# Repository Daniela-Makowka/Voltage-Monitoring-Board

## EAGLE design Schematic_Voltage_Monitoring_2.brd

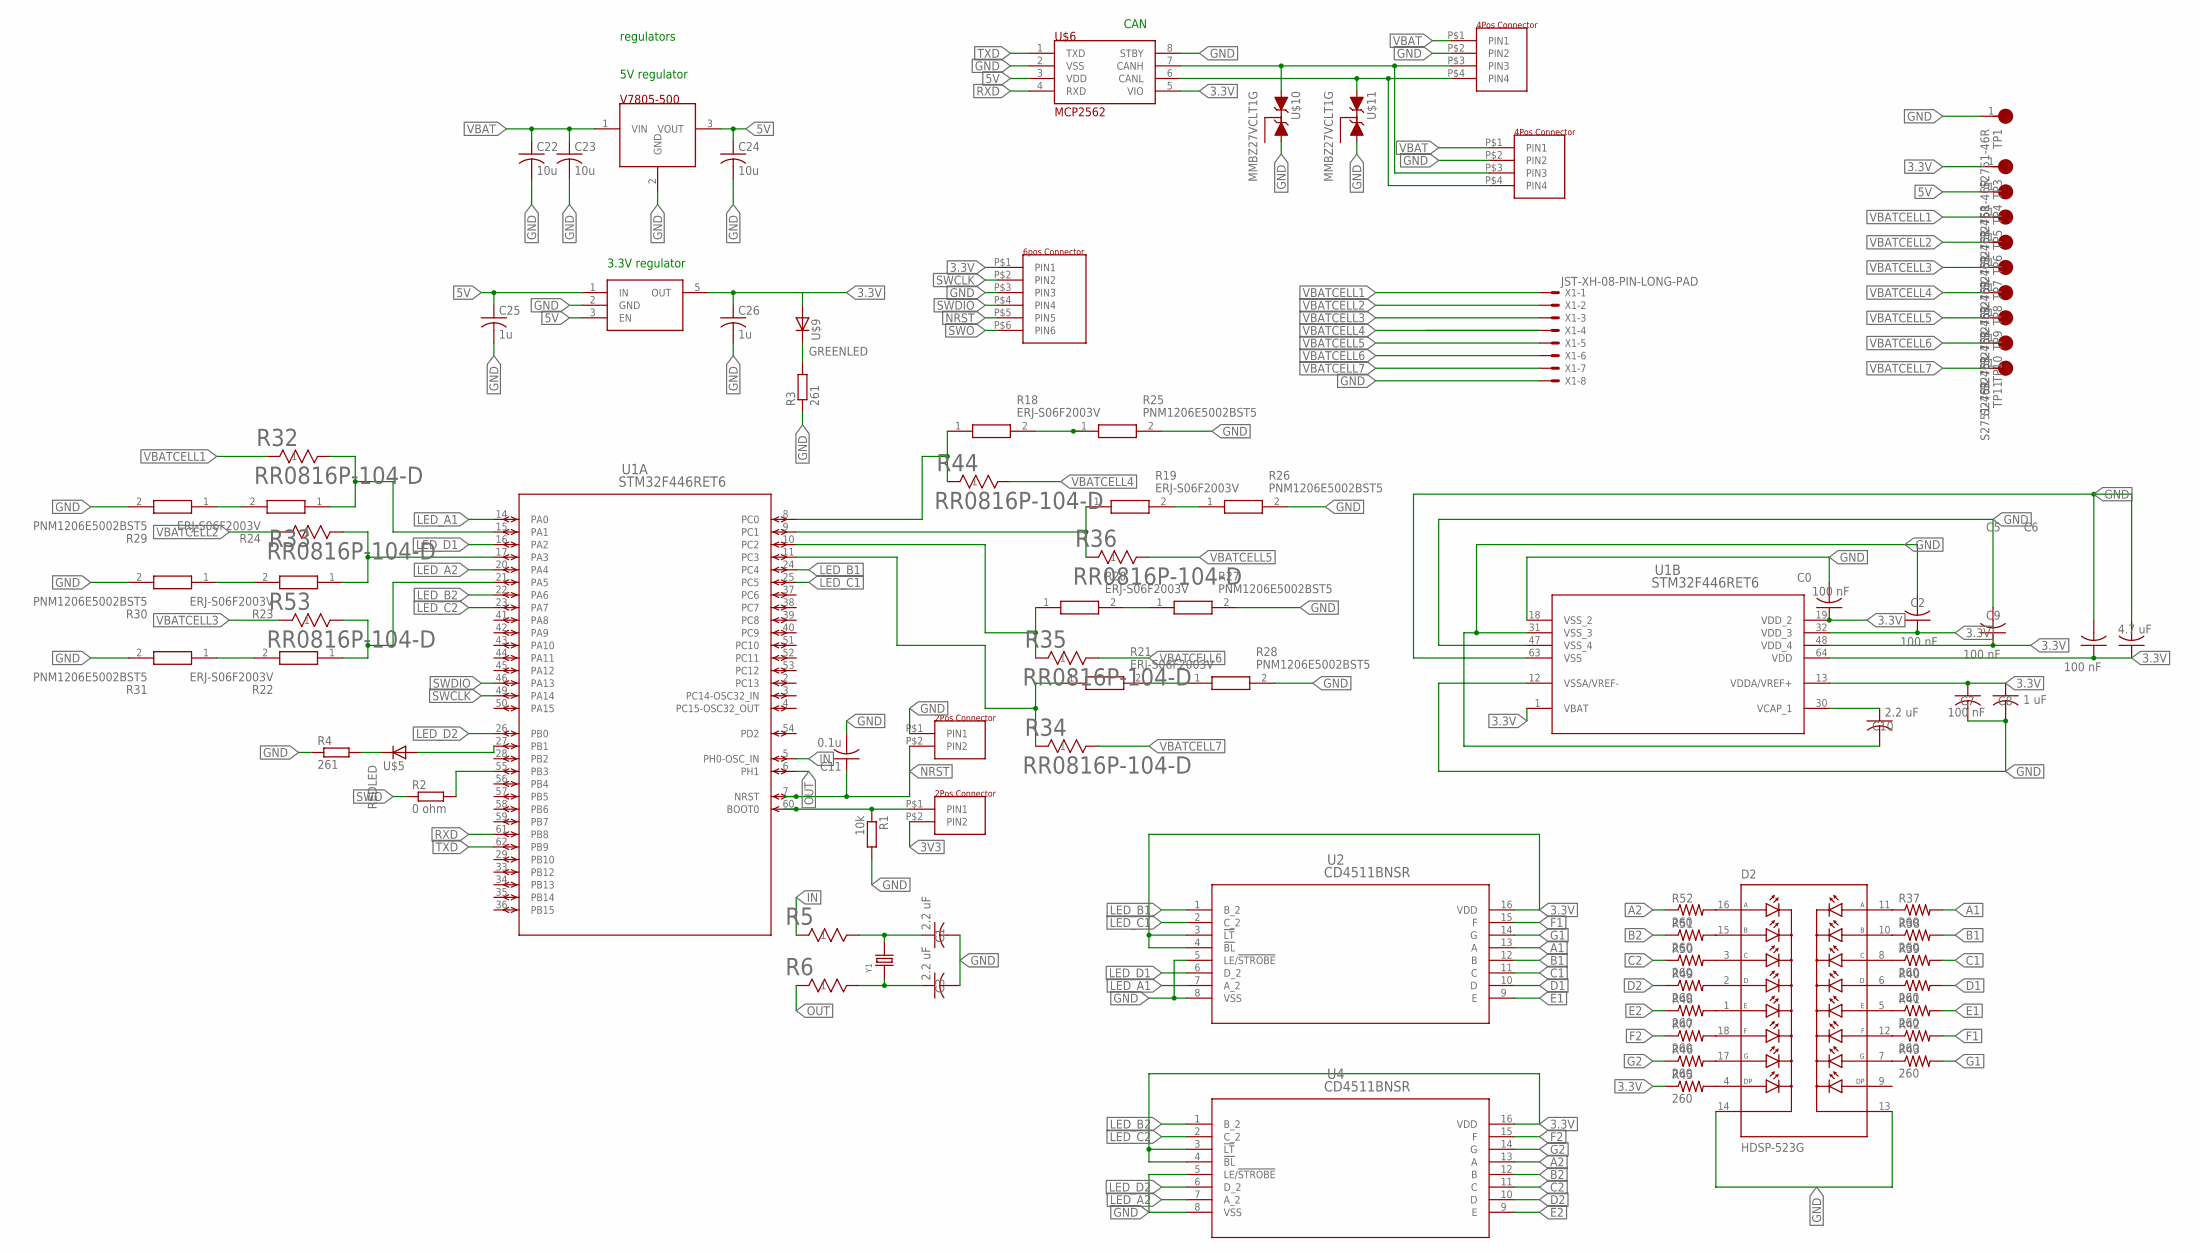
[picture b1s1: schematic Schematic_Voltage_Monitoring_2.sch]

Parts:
C0, C2, C5, C7, C9: 100 nF; C0603
C1, C3, C10: 2.2 uF; C0603
C6: 4.7 uF; C0603
C8: 1 uF; C0603
C11: 0.1u; C1206K
C22, C23, C24: 10u; C1206K
C25, C26: 1u; C1206K
D2: HDSP-523G; LED_HDSP-523G
R1: 10k; R0603
R2: 0 ohm; R0603
R3, R4: 261; R0603
R5, R6, R32, R33, R34, R35, R36, R44, R53: RR0816P-104-D; RES_0816_SUS
R18, R19, R20, R21, R22, R23, R24: ERJ-S06F2003V; ERJS06_U06_(0805)
R25, R26, R27, R28, R29, R30, R31: PNM1206E5002BST5; RESC3216X71N
R37, R38, R39, R40, R41, R42, R43, R45, R46, R47, R48, R49, R50, R51, R52: 260; R0603
TP1, TP3, TP4, TP5, TP6, TP7, TP8, TP9, TP10, TP11: S2751-46R; HARWIN_S2751-46R
U1: STM32F446RET6; LQFP64-10X10MM
U2, U4: CD4511BNSR; NS16
U$1, U$2: 4POS_CONNECTORMOLEX_MICROFIT3.0_RA_4PIN_2ROW; MOLEX_MICROFIT3.0_0430450400
U$3: 6POS_CONNECTOR.1"PITCH_HEADERS; 6POS_HEADER_.1"
U$4, U$7: 2POS_CONNECTOR,.1"HEADER; 2POS_HEADER_.1"
U$5, U$9: LED06033D_0603; LEDC1608X35
U$6: MCP2562; SOIC8
U$8: V7805-500; SIP3
U$10, U$11: MMBZ27VCLT1G; SOT23
U$23: TLV70233DBVR; SOT-23-5
X1: JST-XH-08-PIN-LONG-PAD; JST-XH-08-PACKAGE-LONG-PAD
Y1: DIP-CRYSTAL-16MHZ-18PF-30PPM-40R(HC49US); HC49US

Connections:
3.3V: C0.1, C2.1, C5.1, C6.1, C7.1, C8.1, C9.1, C26.1, R45.1, TP3.1, U1.1 (VBAT), U1.13 (VDDA/VREF+), U1.19 (VDD_2), U1.32 (VDD_3), U1.48 (VDD_4), U1.64 (VDD), U2.3 (!LT), U2.4 (!BL), U2.16 (VDD), U4.3 (!LT), U4.4 (!BL), U4.16 (VDD), U$3.P$1 (PIN1), U$6.5 (VIO), U$9.A, U$23.5 (OUT)
3V3: U$7.P$2 (PIN2)
5V: C24.1, C25.1, TP4.1, U$6.3 (VDD), U$8.3 (VOUT), U$23.1 (IN), U$23.3 (EN)
A1: R37.2, U2.13 (A)
A2: R52.1, U4.13 (A)
B1: R38.2, U2.12 (B)
B2: R51.1, U4.12 (B)
C1: R39.2, U2.11 (C)
C2: R50.1, U4.11 (C)
CANH: U$1.P$3 (PIN3), U$2.P$3 (PIN3), U$6.7 (CANH), U$10.1 (A1)
CANL: U$1.P$4 (PIN4), U$2.P$4 (PIN4), U$6.6 (CANL), U$11.1 (A1)
D1: R40.2, U2.10 (D)
D2: R49.1, U4.10 (D)
E1: R41.2, U2.9 (E)
E2: R48.1, U4.9 (E)
F1: R42.2, U2.15 (F)
F2: R47.1, U4.15 (F)
G1: R43.2, U2.14 (G)
G2: R46.1, U4.14 (G)
GND: C0.2, C1.2, C2.2, C3.2, C5.2, C6.2, C7.2, C8.2, C9.2, C10.2, C11.2, C22.2, C23.2, C24.2, C25.2, C26.2, D2.13 (COM2), D2.14 (COM1), R1.2, R3.1, R4.1, R25.2, R26.2, R27.2, R28.2, R29.2, R30.2, R31.2, TP1.1, U1.12 (VSSA/VREF-), U1.18 (VSS_2), U1.31 (VSS_3), U1.47 (VSS_4), U1.63 (VSS), U2.5 (LE/!STROBE), U2.8 (VSS), U4.5 (LE/!STROBE), U4.8 (VSS), U$1.P$2 (PIN2), U$2.P$2 (PIN2), U$3.P$3 (PIN3), U$4.P$1 (PIN1), U$6.2 (VSS), U$6.8 (STBY), U$8.2 (GND), U$10.2 (A2), U$11.2 (A2), U$23.2 (GND), X1.8
GREENLED: R3.2, U$9.C
IN: R5.1, U1.5 (PH0-OSC_IN)
LED_A1: U1.14 (PA0), U2.7 (A_2)
LED_A2: U1.20 (PA4), U4.7 (A_2)
LED_B1: U1.24 (PC4), U2.1 (B_2)
LED_B2: U1.22 (PA6), U4.1 (B_2)
LED_C1: U1.25 (PC5), U2.2 (C_2)
LED_C2: U1.23 (PA7), U4.2 (C_2)
LED_D1: U1.16 (PA2), U2.6 (D_2)
LED_D2: U1.26 (PB0), U4.6 (D_2)
unnamed: C10.1, U1.30 (VCAP_1)
unnamed: R1.1, U1.60 (BOOT0), U$7.P$1 (PIN1)
unnamed: R2.2, U1.55 (PB3)
unnamed: R19.1, R36.1, U1.9 (PC1)
unnamed: U1.27 (PB1), U$5.A
unnamed: C1.1, R5.2, Y1.2
unnamed: C3.1, R6.2, Y1.1
unnamed: D2.11 (A2), R37.1
unnamed: D2.10 (B2), R38.1
unnamed: D2.8 (C2), R39.1
unnamed: D2.6 (D2), R40.1
unnamed: D2.5 (E2), R41.1
unnamed: D2.12 (F2), R42.1
unnamed: D2.7 (G2), R43.1
unnamed: D2.4 (DP1), R45.2
unnamed: D2.17 (G1), R46.2
unnamed: D2.18 (F1), R47.2
unnamed: D2.1 (E1), R48.2
unnamed: D2.2 (D1), R49.2
unnamed: D2.3 (C1), R50.2
unnamed: D2.15 (B1), R51.2
unnamed: D2.16 (A1), R52.2
unnamed: R18.1, R44.1, U1.8 (PC0)
unnamed: R20.1, R35.1, U1.10 (PC2)
unnamed: R21.1, R34.1, U1.11 (PC3)
unnamed: R24.1, R32.2, U1.15 (PA1)
unnamed: R22.1, R53.2, U1.21 (PA5)
unnamed: R18.2, R25.1
unnamed: R23.1, R33.2, U1.17 (PA3)
unnamed: R19.2, R26.1
unnamed: R20.2, R27.1
unnamed: R21.2, R28.1
unnamed: R24.2, R29.1
unnamed: R23.2, R30.1
unnamed: R22.2, R31.1
NRST: C11.1, U1.7 (NRST), U$3.P$5 (PIN5), U$4.P$2 (PIN2)
OUT: R6.1, U1.6 (PH1)
REDLED: R4.2, U$5.C
RXD: U1.61 (PB8), U$6.4 (RXD)
SWCLK: U1.49 (PA14), U$3.P$2 (PIN2)
SWDIO: U1.46 (PA13), U$3.P$4 (PIN4)
SWO: R2.1, U$3.P$6 (PIN6)
TXD: U1.62 (PB9), U$6.1 (TXD)
VBAT: C22.1, C23.1, U$1.P$1 (PIN1), U$2.P$1 (PIN1), U$8.1 (VIN)
VBATCELL1: R32.1, TP5.1, X1.1
VBATCELL2: R33.1, TP6.1, X1.2
VBATCELL3: R53.1, TP7.1, X1.3
VBATCELL4: R44.2, TP8.1, X1.4
VBATCELL5: R36.2, TP9.1, X1.5
VBATCELL6: R35.2, TP10.1, X1.6
VBATCELL7: R34.2, TP11.1, X1.7

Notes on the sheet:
3.3V regulator
5V regulator
regulators
CAN

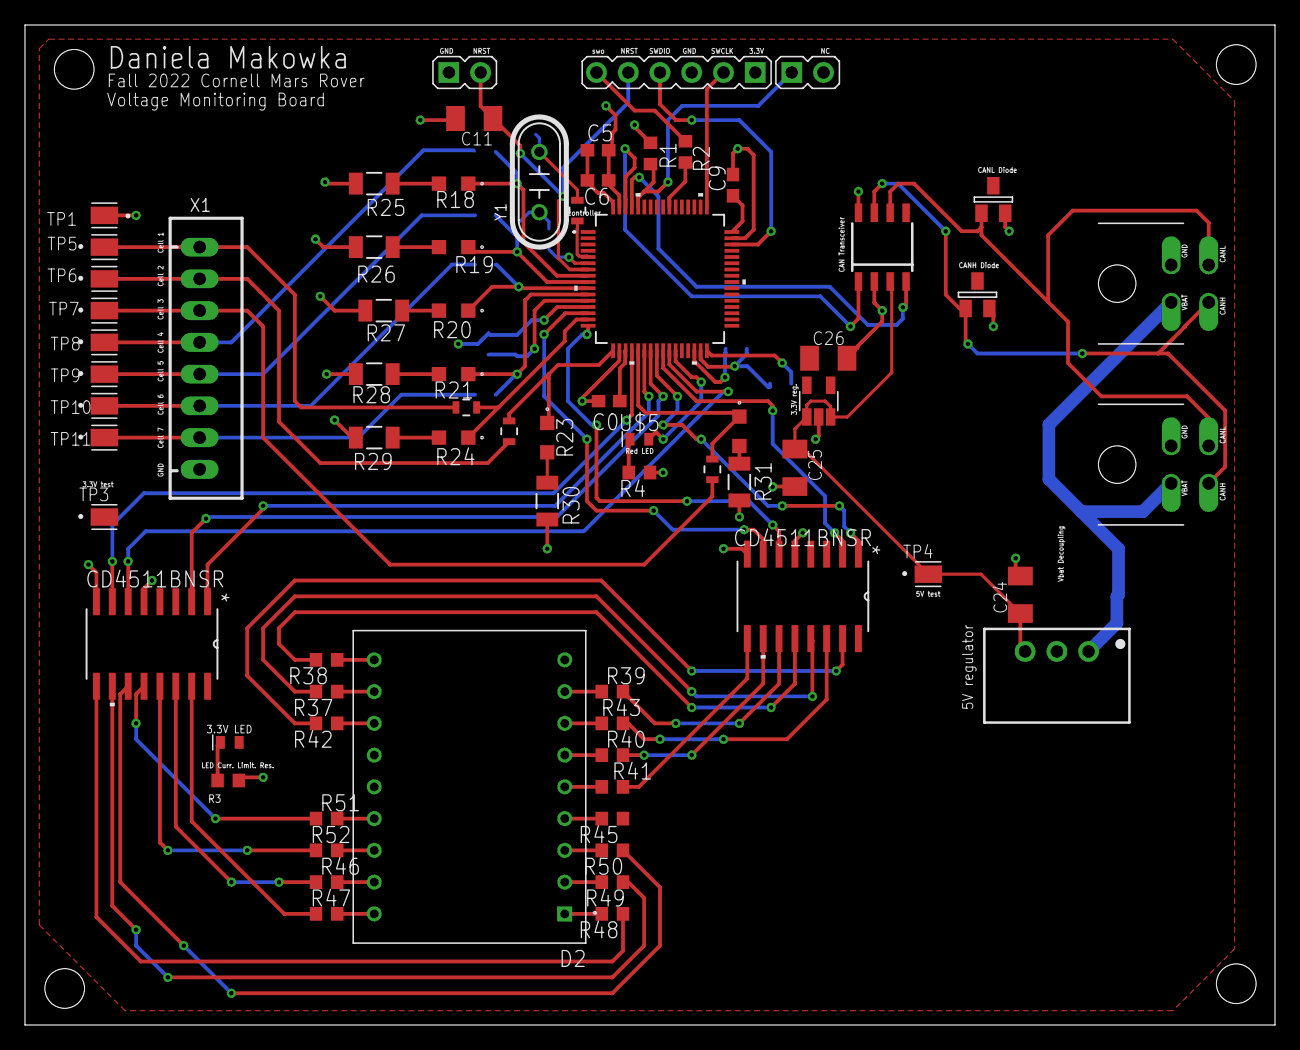
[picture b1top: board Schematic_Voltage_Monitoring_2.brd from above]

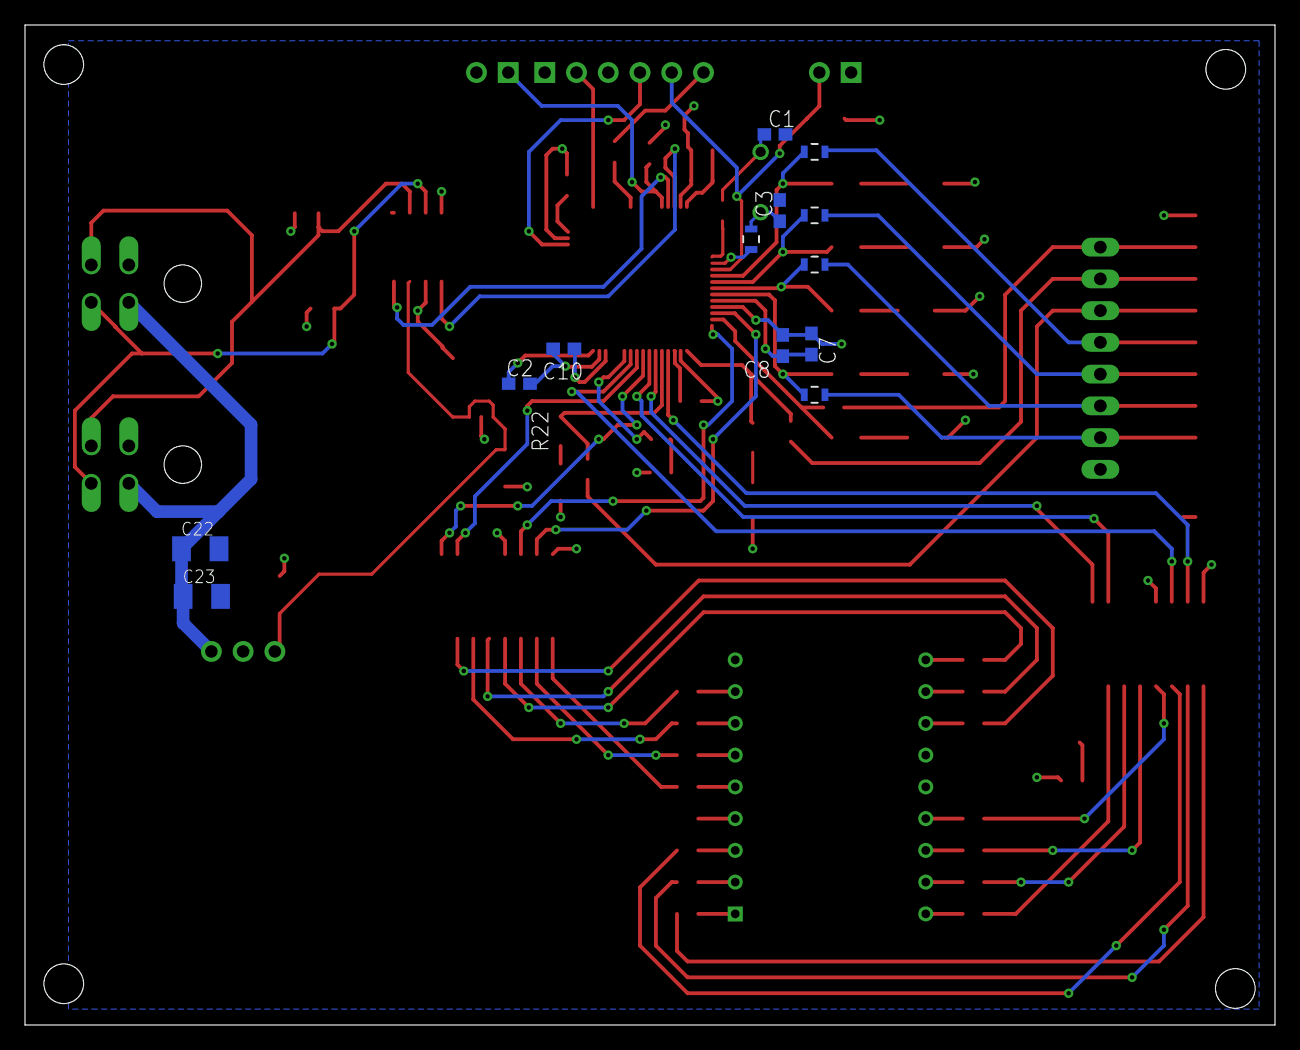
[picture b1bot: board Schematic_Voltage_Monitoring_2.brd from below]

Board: 2 copper layers, 100.0 x 80.0 mm, 86 parts (13 on the bottom side), 80 nets.

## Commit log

2023-10-16 Adding Voltage Monitoring Board files

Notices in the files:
parts and their libraries:
COPYRIGHT: Copyright (C) 2022 Ultra Librarian. All rights reserved.
